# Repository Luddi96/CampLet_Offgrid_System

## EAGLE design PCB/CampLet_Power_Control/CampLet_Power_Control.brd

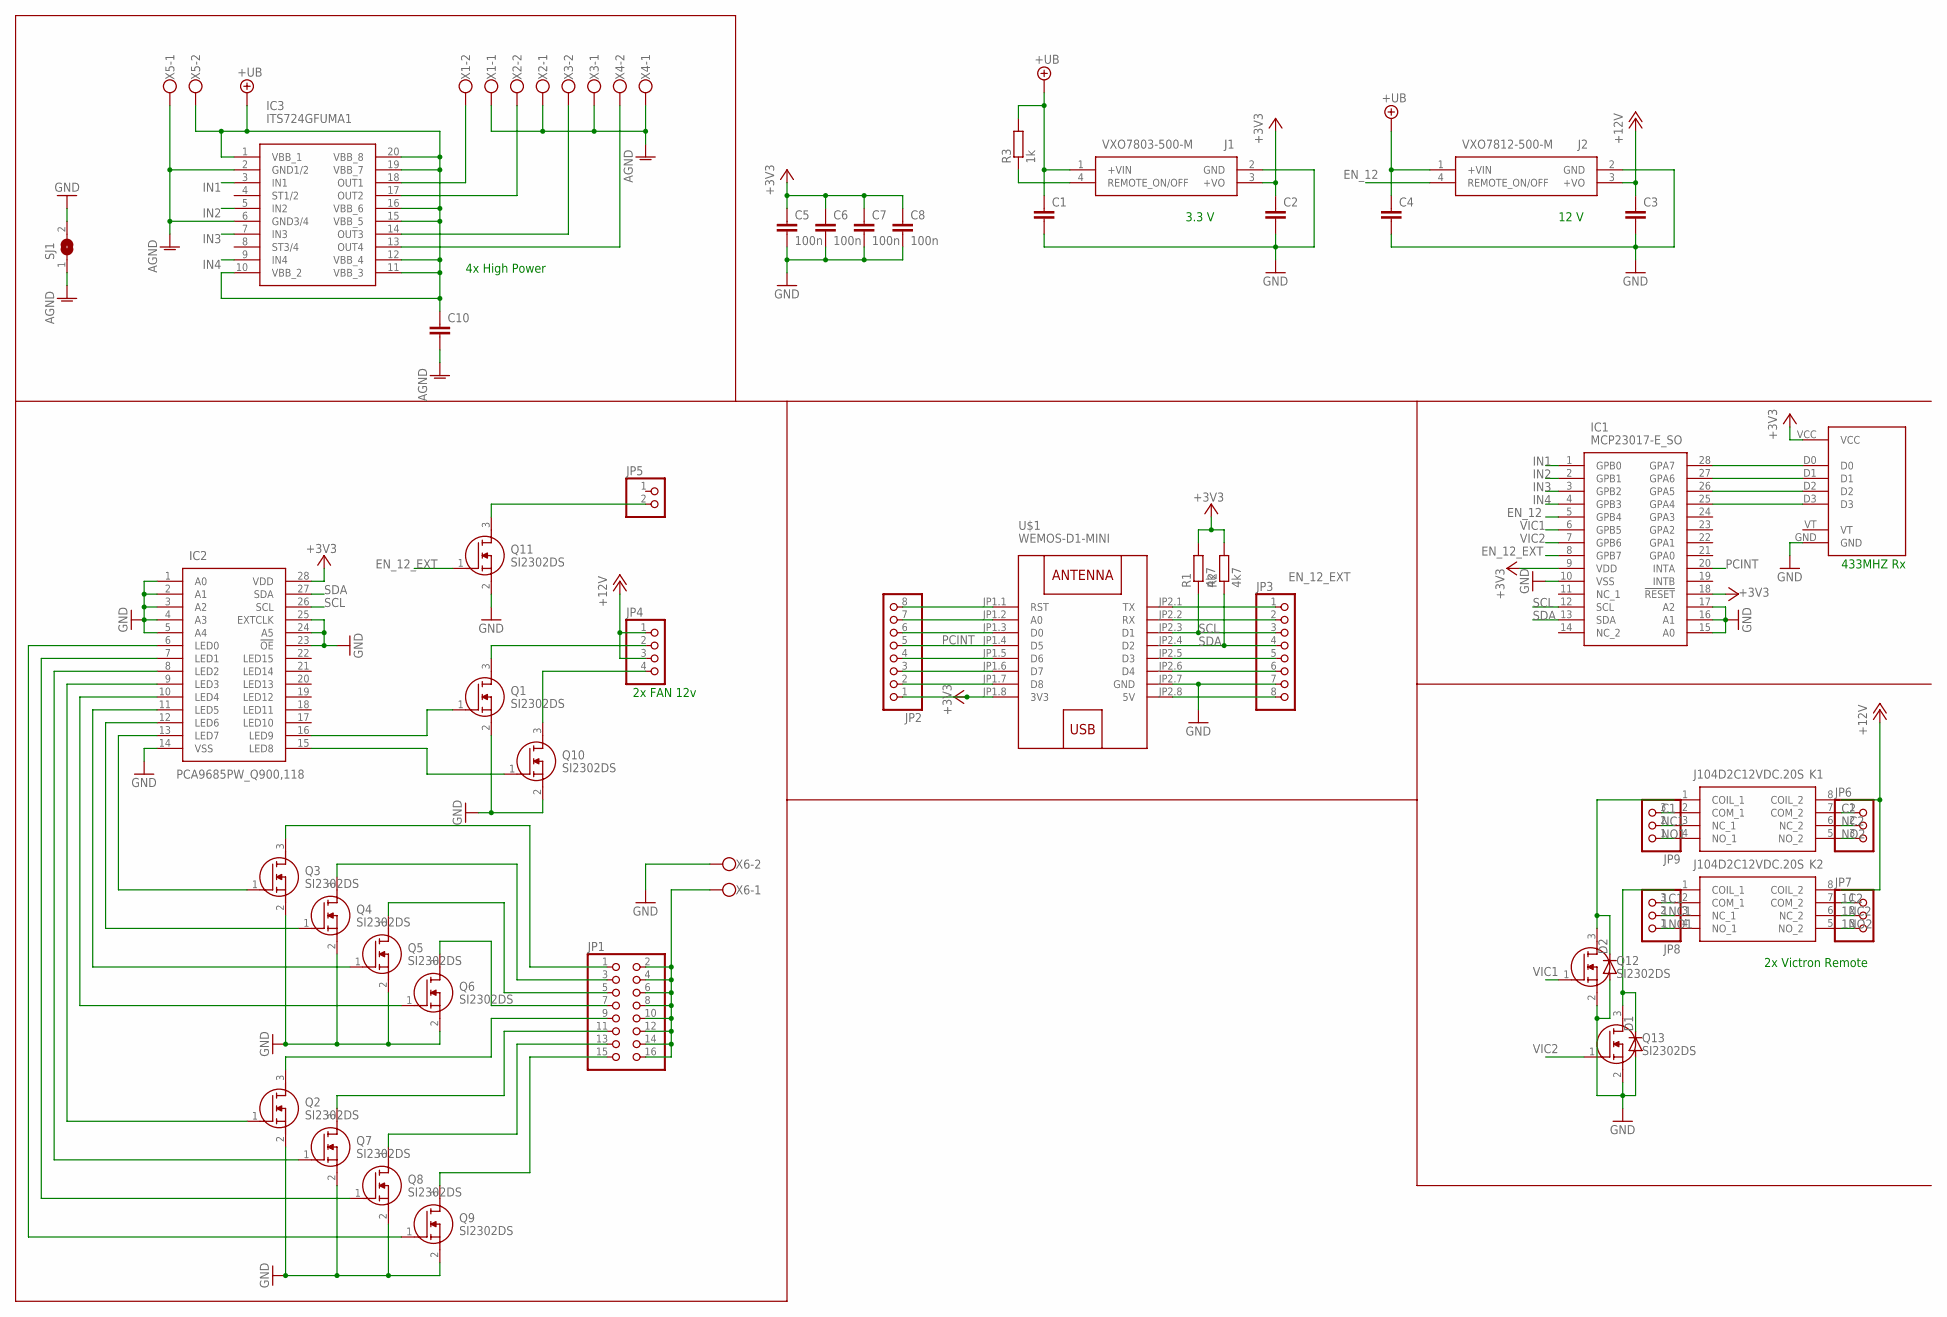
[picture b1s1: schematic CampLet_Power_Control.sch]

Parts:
C1, C4, C10: 10u 30v CL31A106KBHNNNE; C1206
C2: 22u 3.3v CL31A226MOCLNNC; C1206
C3: 22u 12v CL31A226MOCLNNC; C1206
C5, C6, C7, C8: 100n; C0805
D1, D2: 1N4148DO35-7; DO35-7
IC1: MCP23017-E_SO; SOIC127P1030X265-28N
IC2: PCA9685PW_Q900,118; SOP65P640X110-28N
IC3: ITS724GFUMA1; SOIC127P1030X265-20N
J1: VXO7803-500-M; VXO7803500MTR
J2: VXO7812-500-M; VXO7803500MTR
JP1: PINHD-2X8; 2X08
JP2, JP3: PINHD-1X8; 1X08
JP4: PINHD-1X4; 1X04
JP5: PINHD-1X2; 1X02
JP6, JP7, JP8, JP9: PINHD-1X3; 1X03
K1, K2: J104D2C12VDC.20S; J104D2C12VDC20S
Q1, Q2, Q3, Q4, Q5, Q6, Q7, Q8, Q9, Q10, Q11, Q12, Q13: SI2302DS; SOT95P230X110-3N
R1, R2: 4k7; R0805
R3: 1k; R0805
SJ1: SJ
U$1: WEMOS-D1-MINI
U$2: 433MHZ
X1, X2, X3, X4, X5, X6: W237-102

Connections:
1C1: JP8.3, K2.2 (COM_1)
1C2: JP7.1, K2.7 (COM_2)
1NC1: JP8.2, K2.3 (NC_1)
1NC2: JP7.2, K2.6 (NC_2)
1NO1: JP8.1, K2.4 (NO_1)
1NO2: JP7.3, K2.5 (NO_2)
+3V3: C2.1, C5.1, C6.1, C7.1, C8.1, IC1.9 (VDD), IC1.18 (!RESET), IC2.28 (VDD), J1.3 (+VO), JP2.1, R1.2, R2.2, U$1.JP1.8 (3V3), U$2.VCC
+12V: C3.1, J2.3 (+VO), JP4.1, JP4.3, K1.8 (COIL_2), K2.8 (COIL_2)
+UB: C1.1, C4.1, C10.1, IC3.1 (VBB_1), IC3.10 (VBB_2), IC3.11 (VBB_3), IC3.12 (VBB_4), IC3.15 (VBB_5), IC3.16 (VBB_6), IC3.19 (VBB_7), IC3.20 (VBB_8), J1.1 (+VIN), J2.1 (+VIN), R3.2, X5.2
AGND: C10.2, IC3.2 (GND1/2), IC3.6 (GND3/4), SJ1.1, X1.1, X2.1, X3.1, X4.1, X5.1
C1: JP9.3, K1.2 (COM_1)
C2: JP6.1, K1.7 (COM_2)
EN_12: IC1.5 (GPB4), J2.4 (REMOTE_ON/OFF)
EN_12_EXT: IC1.8 (GPB7), Q11.1 (G)
GND: C1.2, C2.2, C3.2, C4.2, C5.2, C6.2, C7.2, C8.2, D1.A, D2.A, IC1.10 (VSS), IC1.15 (A0), IC1.16 (A1), IC1.17 (A2), IC2.1 (A0), IC2.2 (A1), IC2.3 (A2), IC2.4 (A3), IC2.5 (A4), IC2.14 (VSS), IC2.23 (!OE), IC2.24 (A5), IC2.25 (EXTCLK), J1.2 (GND), J2.2 (GND), JP3.7, Q1.2 (S), Q2.2 (S), Q3.2 (S), Q4.2 (S), Q5.2 (S), Q6.2 (S), Q7.2 (S), Q8.2 (S), Q9.2 (S), Q10.2 (S), Q11.2 (S), Q12.2 (S), Q13.2 (S), SJ1.2, U$1.JP2.7 (GND), U$2.GND, X6.2
IN1: IC1.1 (GPB0), IC3.3 (IN1)
IN2: IC1.2 (GPB1), IC3.5 (IN2)
IN3: IC1.3 (GPB2), IC3.7 (IN3)
IN4: IC1.4 (GPB3), IC3.9 (IN4)
unnamed: IC1.28 (GPA7), U$2.D0
unnamed: IC1.27 (GPA6), U$2.D1
unnamed: IC1.26 (GPA5), U$2.D2
unnamed: IC1.25 (GPA4), U$2.D3
unnamed: IC2.12 (LED6), Q4.1 (G)
unnamed: IC2.13 (LED7), Q3.1 (G)
unnamed: IC2.11 (LED5), Q5.1 (G)
unnamed: IC2.10 (LED4), Q6.1 (G)
unnamed: IC2.9 (LED3), Q2.1 (G)
unnamed: IC2.8 (LED2), Q7.1 (G)
unnamed: IC2.7 (LED1), Q8.1 (G)
unnamed: IC2.6 (LED0), Q9.1 (G)
unnamed: JP1.9, Q2.3 (D)
unnamed: JP1.11, Q7.3 (D)
unnamed: JP1.13, Q8.3 (D)
unnamed: JP1.15, Q9.3 (D)
unnamed: JP1.1, Q3.3 (D)
unnamed: JP1.3, Q4.3 (D)
unnamed: JP1.5, Q5.3 (D)
unnamed: JP1.7, Q6.3 (D)
unnamed: JP1.2, JP1.4, JP1.6, JP1.8, JP1.10, JP1.12, JP1.14, JP1.16, X6.1
unnamed: IC3.17 (OUT2), X2.2
unnamed: IC3.14 (OUT3), X3.2
unnamed: IC3.13 (OUT4), X4.2
unnamed: JP3.8, U$1.JP2.8 (5V)
unnamed: IC2.16 (LED9), Q1.1 (G)
unnamed: JP3.6, U$1.JP2.6 (D4)
unnamed: JP3.5, U$1.JP2.5 (D3)
unnamed: JP3.2, U$1.JP2.2 (RX)
unnamed: JP3.1, U$1.JP2.1 (TX)
unnamed: JP2.2, U$1.JP1.7 (D8)
unnamed: JP2.3, U$1.JP1.6 (D7)
unnamed: JP2.4, U$1.JP1.5 (D6)
unnamed: JP2.6, U$1.JP1.3 (D0)
unnamed: JP2.7, U$1.JP1.2 (A0)
unnamed: JP2.8, U$1.JP1.1 (RST)
unnamed: J1.4 (REMOTE_ON/OFF), R3.1
unnamed: IC2.15 (LED8), Q10.1 (G)
unnamed: JP5.2, Q11.3 (D)
unnamed: D2.C, K1.1 (COIL_1), Q12.3 (D)
unnamed: JP4.2, Q1.3 (D)
unnamed: JP4.4, Q10.3 (D)
unnamed: D1.C, K2.1 (COIL_1), Q13.3 (D)
NC1: JP9.2, K1.3 (NC_1)
NC2: JP6.2, K1.6 (NC_2)
NO1: JP9.1, K1.4 (NO_1)
NO2: JP6.3, K1.5 (NO_2)
OUT1: IC3.18 (OUT1), X1.2
PCINT: IC1.20 (INTA), JP2.5, U$1.JP1.4 (D5)
SCL: IC1.12 (SCL), IC2.26 (SCL), JP3.3, R1.1, U$1.JP2.3 (D1)
SDA: IC1.13 (SDA), IC2.27 (SDA), JP3.4, R2.1, U$1.JP2.4 (D2)
VIC1: IC1.6 (GPB5), Q12.1 (G)
VIC2: IC1.7 (GPB6), Q13.1 (G)

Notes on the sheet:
2x FAN 12v
2x Victron Remote
433MHZ Rx
4x High Power
3.3 V
12 V

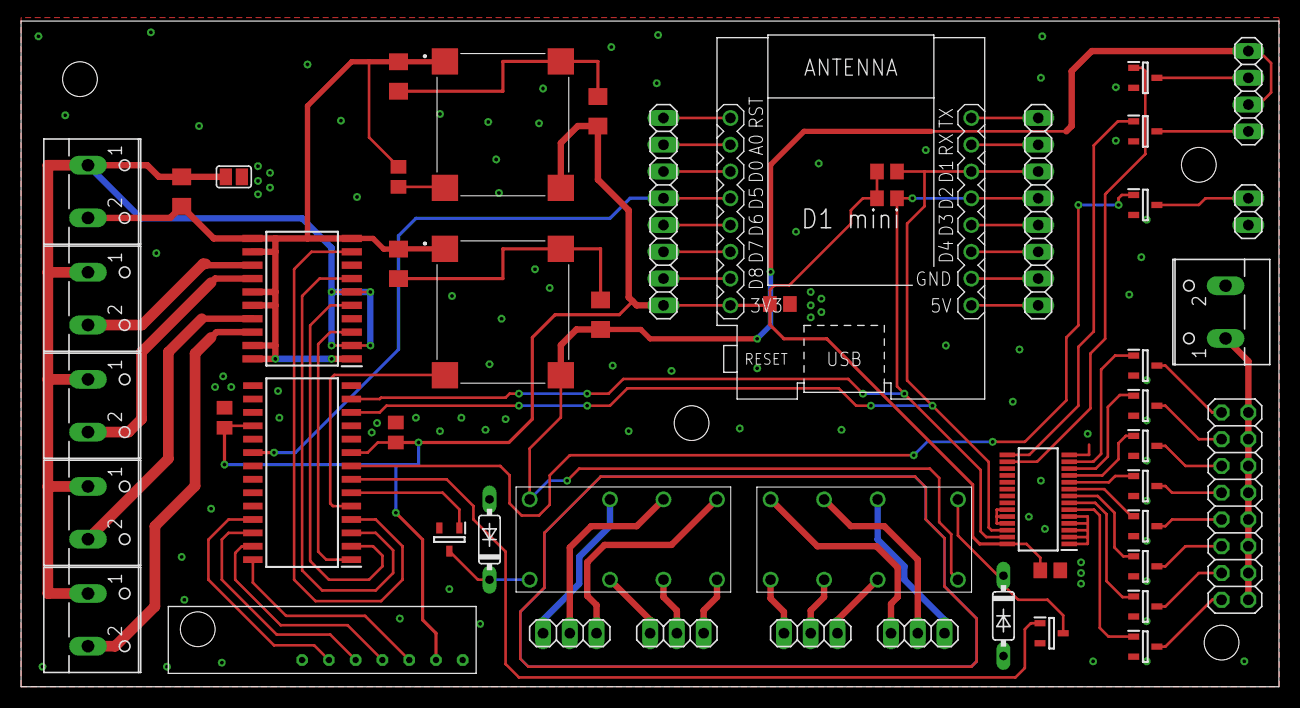
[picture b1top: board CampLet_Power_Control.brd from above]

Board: 2 copper layers, 119.4 x 63.2 mm, 52 parts (0 on the bottom side), 72 nets.

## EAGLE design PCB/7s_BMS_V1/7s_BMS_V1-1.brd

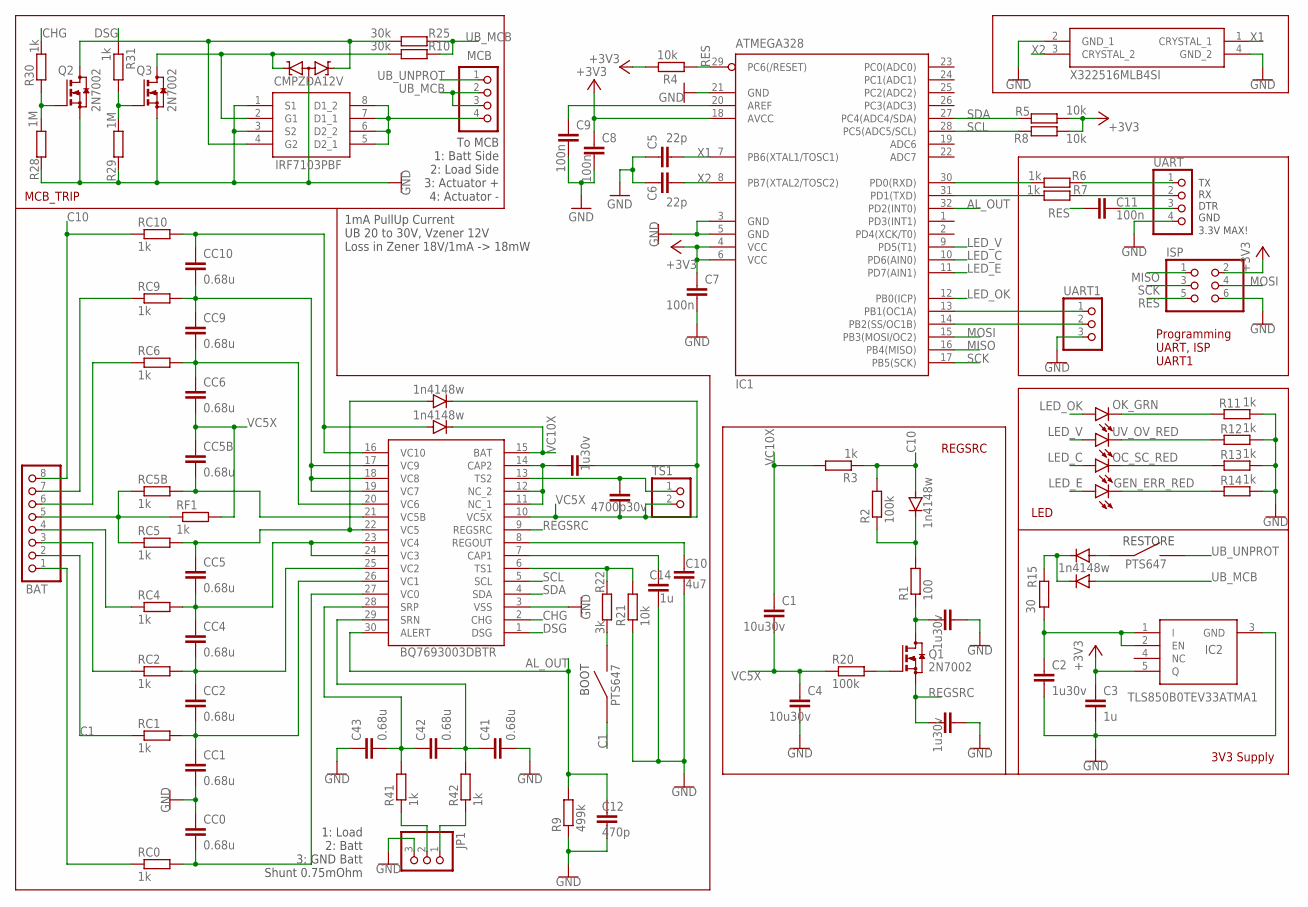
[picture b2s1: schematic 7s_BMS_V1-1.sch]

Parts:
BAT: PINHD-1X8/90; 1X08/90
C1, C4: 10u30v; C0805
C2: 1u30v; C0805
C3, C14: 1u; C0603
C5, C6: 22p; C0603
C7, C8, C9, C11: 100n; C0603
C10: 4u7; C0805
C12: 470p; C0603
C30, C31, C61: 1u30v; C0603
C41, C42, C43: 0.68u; C0603
C62: 4700p30v; C0603
CC0, CC1, CC2, CC4, CC5, CC5B, CC6, CC9, CC10: 0.68u; C0603
D1, D2, D3, D4, D5: 1n4148w; SOD123
GEN_ERR_RED: KT-0603R; CHIP-LED0603
IC1: ATMEGA328; TQFP32-08
IC2: TLS850B0TEV33ATMA1; BTS6143D
IC3: BQ7693003DBTR; SOP50P640X120-30N
ISP: PINHD-2X3; 2X03
JP1: PINHD-1X3/90; 1X03/90
MCB: PINHD-1X4; 1X04
OC_SC_RED: KT-0603R; CHIP-LED0603
OK_GRN: 19-217/GHC-YR1S2/3T; CHIP-LED0603
Q1, Q2, Q3: 2N7002; SOT23
Q4: IRF7103PBF; SOIC127P600X175-8N
R1: 100; R0603
R2, R20: 100k; R0603
R3, R6, R7, R11, R12, R13, R14, R30, R31, R41, R42: 1k; R0603
R4, R5, R8, R21: 10k; R0603
R9: 499k; R0603
R10, R25: 30k; R0603
R15: 30; R0805
R22: 3k; R0603
R28, R29: 1M; R0603
RC0, RC1, RC2, RC4, RC5, RC5B, RC6, RC9, RC10: 1k; R0603
RF1: 1k; R0603
TS1: PINHD-1X2/90; 1X02/90
U$1, U$2: PTS647
U$3: CMPZDA12V; SOT23
UART: PINHD-1X4; 1X04
UART1: PINHD-1X3; 1X03
UV_OV_RED: KT-0603R; CHIP-LED0603
Y1: X322516MLB4SI

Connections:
+3V3: C3.1, C7.1, C8.1, IC1.4 (VCC), IC1.6 (VCC), IC1.18 (AVCC), IC2.5 (Q), ISP.2, R4.2, R5.1, R8.1
A: BAT.5, RC5.1, RC5B.1, RF1.1
AL_OUT: C12.1, IC1.32 (PD2(INT0)), IC3.30 (ALERT), R9.2
C1: BAT.2, RC1.1, U$2.1, U$2.2
C10: BAT.8, D5.A, R2.2, R3.1, RC10.1
CHG: IC3.2 (CHG), R30.2
DSG: IC3.1 (DSG), R31.1
GND: C2.2, C3.2, C4.2, C5.1, C6.1, C7.2, C8.2, C9.2, C10.2, C12.2, C14.2, C30.1, C31.1, C41.2, C43.1, CC0.1, CC1.2, IC1.3 (GND), IC1.5 (GND), IC1.21 (GND), IC2.3 (GND), IC3.3 (VSS), ISP.6, JP1.3, Q2.2 (S), Q3.2 (S), Q4.1 (S1), Q4.3 (S2), R9.1, R11.1, R12.1, R13.1, R14.1, R21.1, R28.1, R29.2, U$3.3 (A), UART.4, UART1.3, Y1.2 (GND_1), Y1.4 (GND_2)
LED_C: IC1.10 (PD6(AIN0)), OC_SC_RED.A
LED_E: GEN_ERR_RED.A, IC1.11 (PD7(AIN1))
LED_OK: IC1.12 (PB0(ICP)), OK_GRN.A
LED_V: IC1.9 (PD5(T1)), UV_OV_RED.A
MISO: IC1.16 (PB4(MISO)), ISP.1
MOSI: IC1.15 (PB3(MOSI/OC2)), ISP.4
unnamed: C2.1, IC2.1 (I), IC2.2 (EN), R15.1
unnamed: CC10.1, D3.A, IC3.16 (VC10), RC10.2
unnamed: D2.A, U$1.1, U$1.2
unnamed: C30.2, Q1.3 (D), R1.1
unnamed: CC0.2, IC3.27 (VC0), RC0.2
unnamed: C61.1, IC3.11 (NC_1), IC3.12 (NC_2), IC3.14 (CAP2)
unnamed: CC1.1, CC2.2, IC3.26 (VC1), RC1.2
unnamed: CC2.1, CC4.2, IC3.25 (VC2), RC2.2
unnamed: CC4.1, CC5.2, IC3.23 (VC4), IC3.24 (VC3), RC4.2
unnamed: BAT.1, RC0.1
unnamed: BAT.4, RC4.1
unnamed: IC1.30 (PD0(RXD)), R6.2
unnamed: C9.1, IC1.20 (AREF)
unnamed: BAT.3, RC2.1
unnamed: IC1.31 (PD1(TXD)), R7.2
unnamed: R6.1, UART.1
unnamed: R7.1, UART.2
unnamed: C11.2, UART.3
unnamed: C42.1, C43.2, IC3.28 (SRP), R41.2
unnamed: CC5.1, D4.A, IC3.22 (VC5), RC5.2
unnamed: CC5B.2, IC3.21 (VC5B), RC5B.2
unnamed: BAT.7, RC9.1
unnamed: BAT.6, RC6.1
unnamed: CC9.1, CC10.2, IC3.17 (VC9), IC3.18 (VC8), IC3.19 (VC7), RC9.2
unnamed: CC6.1, CC9.2, IC3.20 (VC6), RC6.2
unnamed: C62.2, IC3.13 (TS2), TS1.1
unnamed: Q1.1 (G), R20.2
unnamed: C10.1, IC3.8 (REGOUT)
unnamed: D5.C, R1.2, R2.1
unnamed: C14.1, IC3.7 (CAP1)
unnamed: IC3.6 (TS1), R21.2, R22.2
unnamed: R22.1, U$2.3, U$2.4
unnamed: C41.1, C42.2, IC3.29 (SRN), R42.2
unnamed: JP1.2, R41.1
unnamed: JP1.1, R42.1
unnamed: Q2.1 (G), R28.2, R30.1
unnamed: Q3.1 (G), R29.1, R31.2
unnamed: MCB.4, Q4.5 (D2_1), Q4.6 (D2_2), Q4.7 (D1_1), Q4.8 (D1_2)
unnamed: D1.C, D2.C, R15.2
unnamed: Q3.3 (D), Q4.2 (G1), R10.1, U$3.1 (K2)
unnamed: GEN_ERR_RED.C, R14.2
unnamed: OC_SC_RED.C, R13.2
unnamed: R12.2, UV_OV_RED.C
unnamed: OK_GRN.C, R11.2
unnamed: IC1.14 (PB2(SS/OC1B)), UART1.2
unnamed: IC1.13 (PB1(OC1A)), UART1.1
REGSRC: C31.2, IC3.9 (REGSRC), Q1.2 (S)
RES: C11.1, IC1.29 (PC6(/RESET)), ISP.5, R4.1
SCK: IC1.17 (PB5(SCK)), ISP.3
SCL: IC1.28 (PC5(ADC5/SCL)), IC3.5 (SCL), R8.2
SDA: IC1.27 (PC4(ADC4/SDA)), IC3.4 (SDA), R5.2
TRIP_MCB: Q2.3 (D), Q4.4 (G2), R25.1, U$3.2 (K1)
UB_MCB: D1.A, MCB.2, MCB.3, R10.2, R25.2
UB_UNPROT: MCB.1, U$1.3, U$1.4
VC5X: C1.2, C4.1, C61.2, C62.1, CC5B.1, CC6.2, D4.C, IC3.10 (VC5X), R20.1, RF1.2, TS1.2
VC10X: C1.1, D3.C, IC3.15 (BAT), R3.2
X1: C5.2, IC1.7 (PB6(XTAL1/TOSC1)), Y1.1 (CRYSTAL_1)
X2: C6.2, IC1.8 (PB7(XTAL2/TOSC2)), Y1.3 (CRYSTAL_2)

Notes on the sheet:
TX RX DTR GND
3.3V MAX!
Programming UART, ISP UART1
3V3 Supply
RESTORE
REGSRC
1: Load 2: Batt 3: GND Batt Shunt 0.75mOhm
BOOT
1mA PullUp Current UB 20 to 30V, Vzener 12V Loss in Zener 18V/1mA -> 18mW
LED
MCB_TRIP
To MCB 1: Batt Side 2: Load Side 3: Actuator + 4: Actuator -

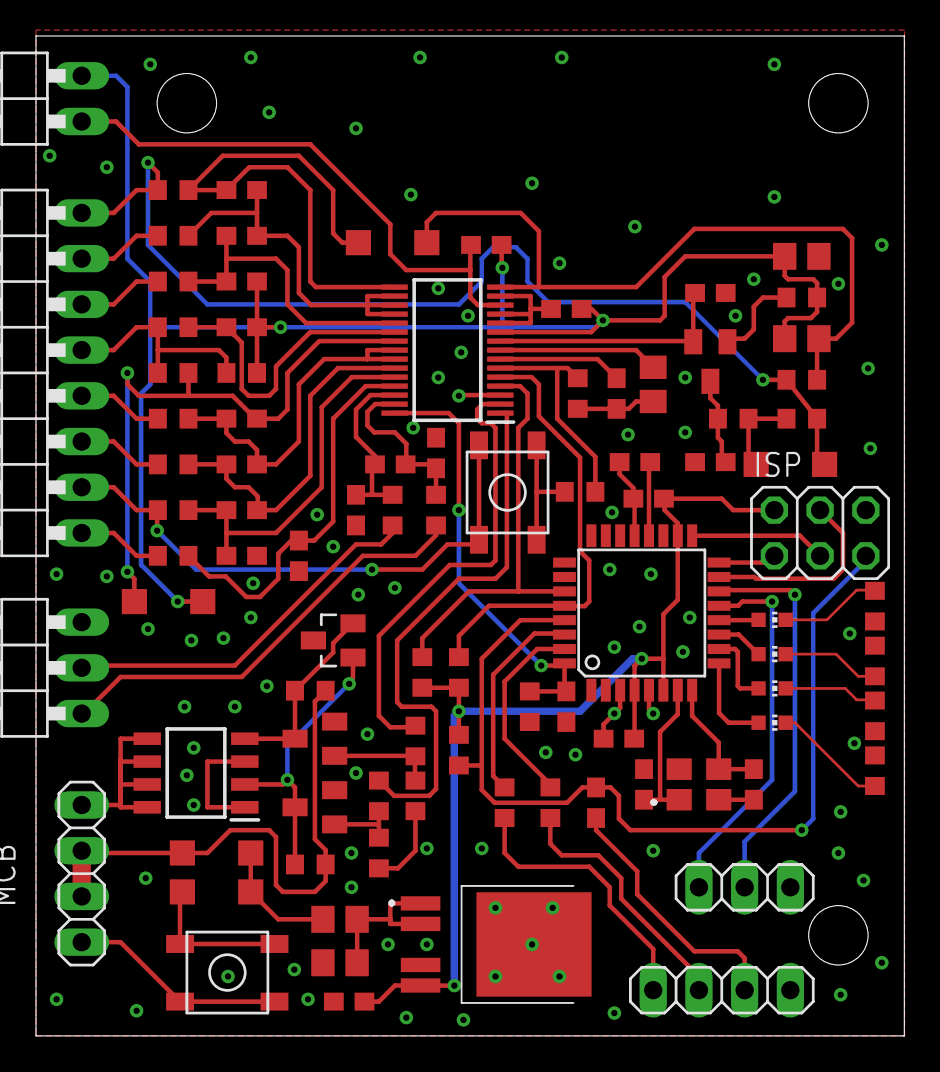
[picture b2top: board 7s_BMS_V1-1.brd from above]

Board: 2 copper layers, 48.2 x 55.5 mm, 91 parts (0 on the bottom side), 72 nets.

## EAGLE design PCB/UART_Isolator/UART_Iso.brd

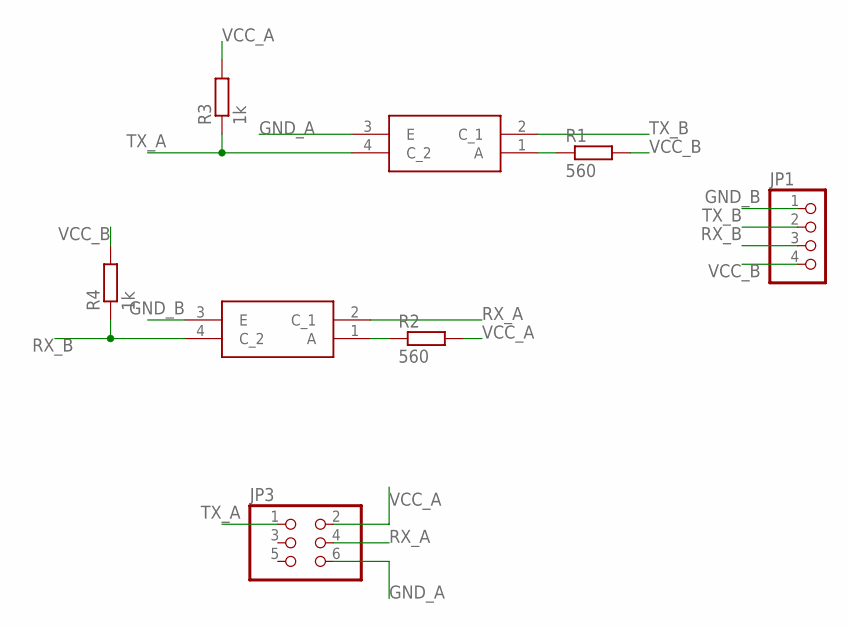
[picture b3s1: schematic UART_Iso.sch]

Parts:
JP1: PINHD-1X4/90; 1X04/90
JP3: PINHD-2X3; 2X03
Q1, Q2: SFH6186-5T; SOP254P978X406-4N
R1, R2: 560; R0805
R3, R4: 1k; R0805

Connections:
GND_A: JP3.6, Q2.3 (E)
GND_B: JP1.1, Q1.3 (E)
unnamed: Q2.1 (A), R1.1
unnamed: Q1.1 (A), R2.1
RX_A: JP3.4, Q1.2 (C_1)
RX_B: JP1.3, Q1.4 (C_2), R4.1
TX_A: JP3.1, Q2.4 (C_2), R3.1
TX_B: JP1.2, Q2.2 (C_1)
VCC_A: JP3.2, R2.2, R3.2
VCC_B: JP1.4, R1.2, R4.2

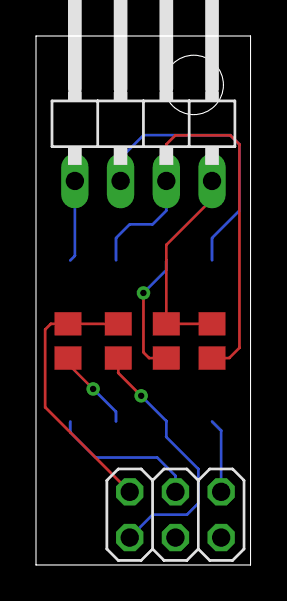
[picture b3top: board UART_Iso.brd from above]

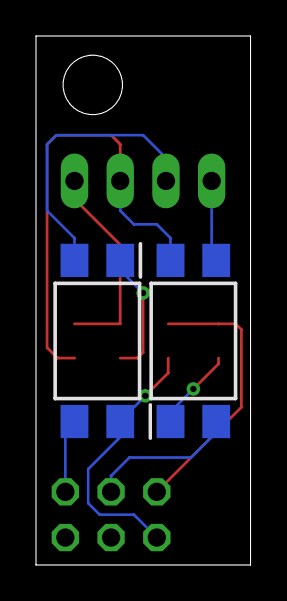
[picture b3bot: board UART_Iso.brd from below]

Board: 2 copper layers, 11.9 x 29.4 mm, 8 parts (2 on the bottom side), 10 nets.

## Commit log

2021-06-12 added settings page

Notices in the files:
parts and their libraries:
diy-modules: Released under the Creative Commons Attribution 4.0 International License: http://creativecommons.org/licenses/by/4.0
